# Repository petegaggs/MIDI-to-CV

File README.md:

# MIDI-to-CV
arduino based MIDI to CV converter
2 variants:
Original hardware was simple 1V/octave midi to CV converter
New version is combined Midi-CV plus AS3340 VCO module

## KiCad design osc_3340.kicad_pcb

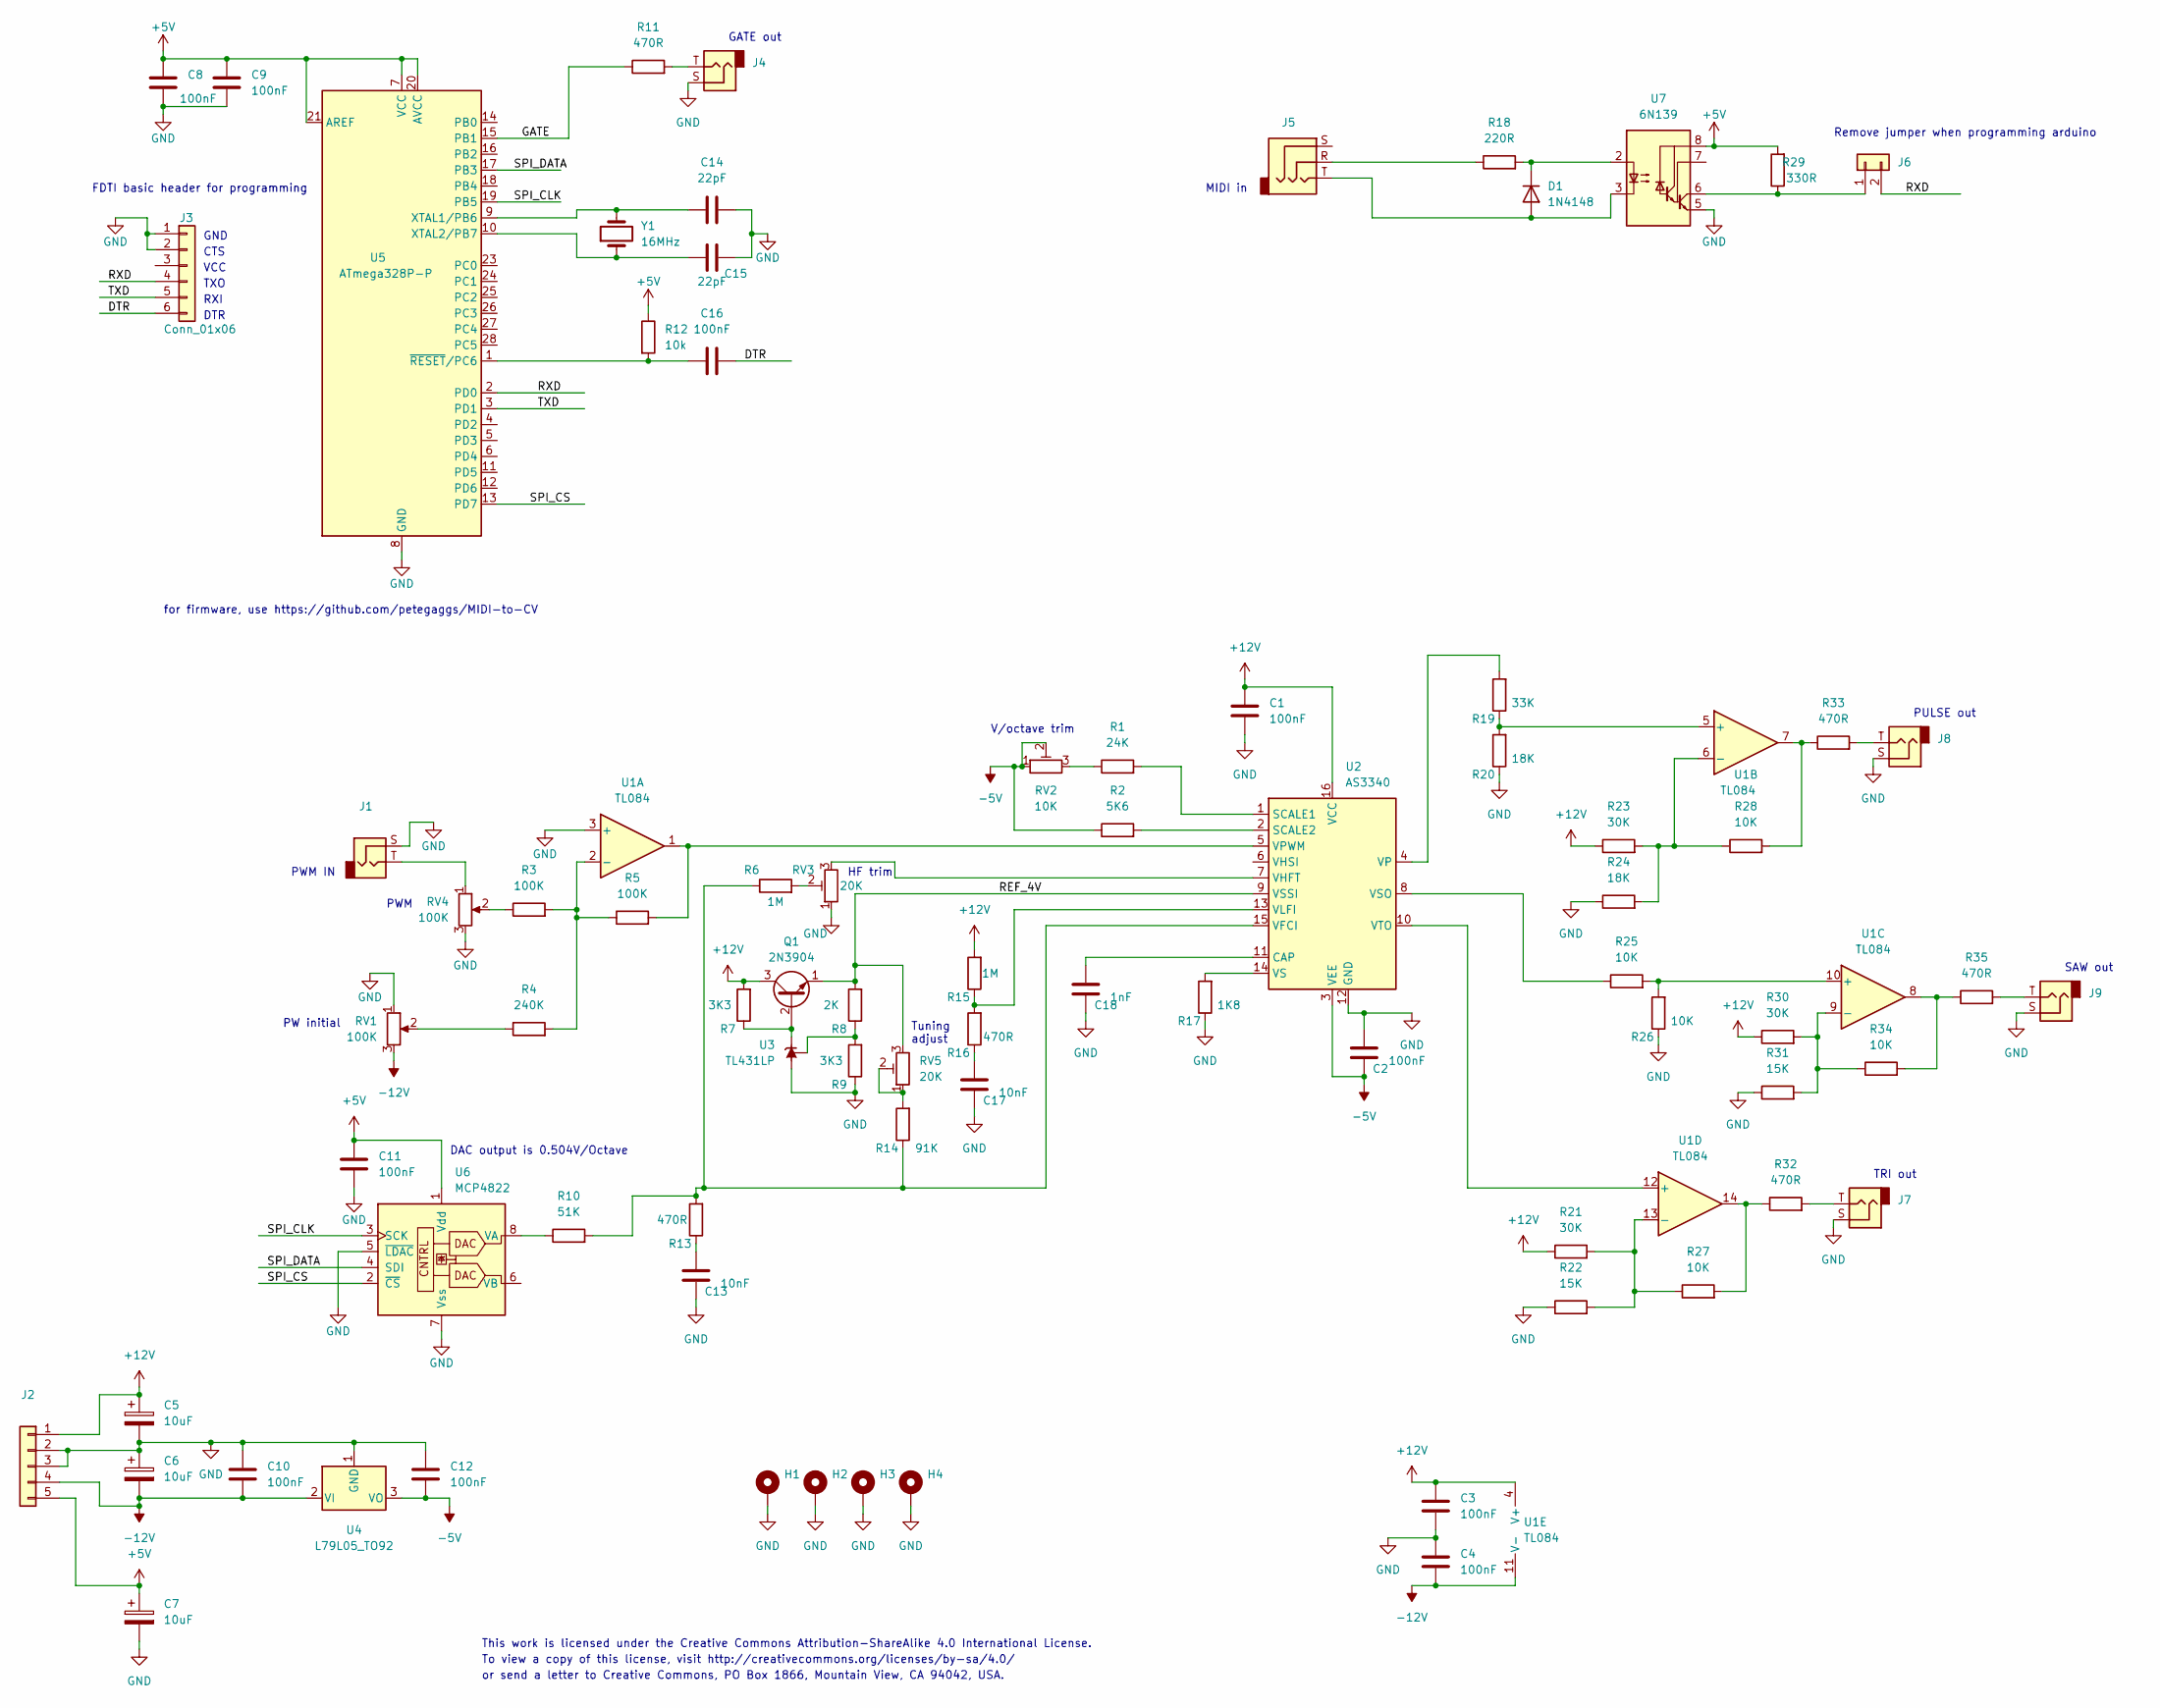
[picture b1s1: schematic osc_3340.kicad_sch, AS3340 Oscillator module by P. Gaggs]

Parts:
C1, C2, C3, C4, C8, C9, C10, C11, C12, C16: 100nF; C_0805_2012Metric_Pad1.18x1.45mm_HandSolder
C5, C6, C7: 10uF; CP_Radial_D5.0mm_P2.00mm
C13, C17: 10nF; C_0805_2012Metric_Pad1.18x1.45mm_HandSolder
C14, C15: 22pF; C_0805_2012Metric_Pad1.18x1.45mm_HandSolder
C18: 1nF; C_Disc_D6.0mm_W4.4mm_P5.00mm
D1: 1N4148; D_DO-35_SOD27_P7.62mm_Horizontal
H1, H2, H3, H4: MountingHole_Pad; MountingHole_3.2mm_M3_ISO7380_Pad
J1, J4, J7, J8, J9: AudioJack2; jack_3.5mm_mono_vertical_soundtronics_7212-239
J2: Conn_01x05; PinHeader_1x05_P2.54mm_Vertical
J3: Conn_01x06; PinHeader_1x06_P2.54mm_Vertical
J5: AudioJack3; jack_3.5mm_stereo_vertical_soundtronics_7212-240
J6: Conn_01x02; PinHeader_1x02_P2.54mm_Vertical
Q1: 2N3904; TO-92_Inline_Wide
R1: 24K; R_0805_2012Metric_Pad1.20x1.40mm_HandSolder
R2: 5K6; R_0805_2012Metric_Pad1.20x1.40mm_HandSolder
R3, R5: 100K; R_0805_2012Metric_Pad1.20x1.40mm_HandSolder
R4: 240K; R_0805_2012Metric_Pad1.20x1.40mm_HandSolder
R6, R15: 1M; R_0805_2012Metric_Pad1.20x1.40mm_HandSolder
R7, R9: 3K3; R_0805_2012Metric_Pad1.20x1.40mm_HandSolder
R8: 2K; R_0805_2012Metric_Pad1.20x1.40mm_HandSolder
R10: 51K; R_0805_2012Metric_Pad1.20x1.40mm_HandSolder
R11, R13, R16, R32, R33, R35: 470R; R_0805_2012Metric_Pad1.20x1.40mm_HandSolder
R12: 10k; R_0805_2012Metric_Pad1.20x1.40mm_HandSolder
R14: 91K; R_0805_2012Metric_Pad1.20x1.40mm_HandSolder
R17: 1K8; R_0805_2012Metric_Pad1.20x1.40mm_HandSolder
R18: 220R; R_0805_2012Metric_Pad1.20x1.40mm_HandSolder
R19: 33K; R_0805_2012Metric_Pad1.20x1.40mm_HandSolder
R20, R24: 18K; R_0805_2012Metric_Pad1.20x1.40mm_HandSolder
R21, R23, R30: 30K; R_0805_2012Metric_Pad1.20x1.40mm_HandSolder
R22, R31: 15K; R_0805_2012Metric_Pad1.20x1.40mm_HandSolder
R25, R26, R27, R28, R34: 10K; R_0805_2012Metric_Pad1.20x1.40mm_HandSolder
R29: 330R; R_0805_2012Metric_Pad1.20x1.40mm_HandSolder
RV1, RV4: 100K; Potentiometer_Alps_RK09K_Single_Vertical
RV2: 10K; Potentiometer_Bourns_3296W_Vertical
RV3, RV5: 20K; Potentiometer_Bourns_3296W_Vertical
U1: TL084; DIP-14_W7.62mm_Socket
U2: AS3340; DIP-16_W7.62mm_Socket
U3: TL431LP; TO-92_Inline_Wide
U4: L79L05_TO92; TO-92_Inline_Wide
U5: ATmega328P-P; DIP-28_W7.62mm
U6: MCP4822; DIP-8_W7.62mm_Socket
U7: 6N139; DIP-8_W7.62mm_Socket
Y1: 16MHz; Crystal_HC49-4H_Vertical

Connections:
+5V: C7.1, C8.1, C9.1, C11.1, J2.5, R12.1, R29.2, U5.7 (VCC), U5.20 (AVCC), U5.21 (AREF), U6.1 (Vdd), U7.8 (VCC)
+12V: C1.1, C3.1, C5.1, J2.1, Q1.3 (C), R7.2, R15.2, R21.1, R23.1, R30.1, U1.4 (V+), U2.16 (VCC)
-5V: C2.2, C12.2, R2.1, RV2.1, RV2.2, U2.3 (VEE), U4.3 (VO)
-12V: C4.2, C6.2, C10.2, J2.4, RV1.3, U1.11 (V-), U4.2 (VI)
/DTR: C16.2, J3.6
/GATE: R11.1, U5.15 (PB1)
/REF_4V: Q1.1 (E), R8.2, RV5.3, U2.9 (VSSI)
/RXD: J3.4, J6.2, U5.2 (PD0)
/SPI_CLK: U5.19 (PB5), U6.3 (SCK)
/SPI_CS: U5.13 (PD7), U6.2 (~CS)
/SPI_DATA: U5.17 (PB3), U6.4 (SDI)
/TXD: J3.5, U5.3 (PD1)
GND: C1.2, C2.1, C3.2, C4.1, C5.2, C6.1, C7.2, C8.2, C9.2, C10.1, C11.2, C12.1, C13.2, C14.2, C15.2, C17.2, C18.2, H1.1, H2.1, H3.1, H4.1, J1.S, J2.2, J2.3, J3.1, J3.2, J4.S, J7.S, J8.S, J9.S, R9.1, R17.1, R20.1, R22.1, R24.1, R26.1, R31.1, RV1.1, RV3.1, RV4.3, U1.3 (+), U2.12 (GND), U3.2 (A), U4.1 (GND), U5.8 (GND), U5.22 (GND), U6.5 (~LDAC), U6.7 (Vss), U7.5 (GND)
unnamed: C13.1, R13.1
unnamed: C14.1, U5.9 (XTAL1/PB6), Y1.2
unnamed: C15.1, U5.10 (XTAL2/PB7), Y1.1
unnamed: C16.1, R12.2, U5.1 (~RESET/PC6)
unnamed: C17.1, R16.1
unnamed: C18.1, U2.11 (CAP)
unnamed: D1.1 (K), R18.2, U7.2 (C1)
unnamed: D1.2 (A), J5.T, U7.3 (C2)
unnamed: J1.T, RV4.1
unnamed: J4.T, R11.2
unnamed: J5.R, R18.1
unnamed: J6.1, R29.1, U7.6 (VO2)
unnamed: J7.T, R32.2
unnamed: J8.T, R33.2
unnamed: J9.T, R35.2
unnamed: Q1.2 (B), R7.1, U3.3 (K)
unnamed: R1.1, RV2.3
unnamed: R1.2, U2.1 (SCALE1)
unnamed: R2.2, U2.2 (SCALE2)
unnamed: R3.1, RV4.2
unnamed: R3.2, R4.2, R5.1, U1.2 (-)
unnamed: R4.1, RV1.2
unnamed: R5.2, U1.1, U2.5 (VPWM)
unnamed: R6.2, RV3.2
unnamed: R8.1, R9.2, U3.1 (REF)
unnamed: R10.1, U6.8 (VA)
unnamed: R6.1, R10.2, R13.2, R14.1, U2.15 (VFCI)
unnamed: R14.2, RV5.1, RV5.2
unnamed: R15.1, R16.2, U2.13 (VLFI)
unnamed: R17.2, U2.14 (VS)
unnamed: R19.1, R20.2, U1.5 (+)
unnamed: R19.2, U2.4 (VP)
unnamed: R21.2, R22.2, R27.1, U1.13 (-)
unnamed: R23.2, R24.2, R28.1, U1.6 (-)
unnamed: R25.1, U2.8 (VSO)
unnamed: R25.2, R26.2, U1.10 (+)
unnamed: R27.2, R32.1, U1.14
unnamed: R28.2, R33.1, U1.7
unnamed: R30.2, R31.2, R34.1, U1.9 (-)
unnamed: R34.2, R35.1, U1.8
unnamed: RV3.3, U2.7 (VHFT)
unnamed: U1.12 (+), U2.10 (VTO)

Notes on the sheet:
HF trim
PWM IN
FDTI basic header for programming
for firmware, use https://github.com/petegaggs/MIDI-to-CV
GATE out
GND
V/octave trim
Tuning adjust
VCC
This work is licensed under the Creative Commons Attribution-ShareAlike 4.0 International License.
RXI
DAC output is 0.504V/Octave
TRI out
PW initial
TXO
SAW out
PWM
Remove jumper when programming arduino
or send a letter to Creative Commons, PO Box 1866, Mountain View, CA 94042, USA.
To view a copy of this license, visit http://creativecommons.org/licenses/by-sa/4.0/
PULSE out
DTR
MIDI in
CTS

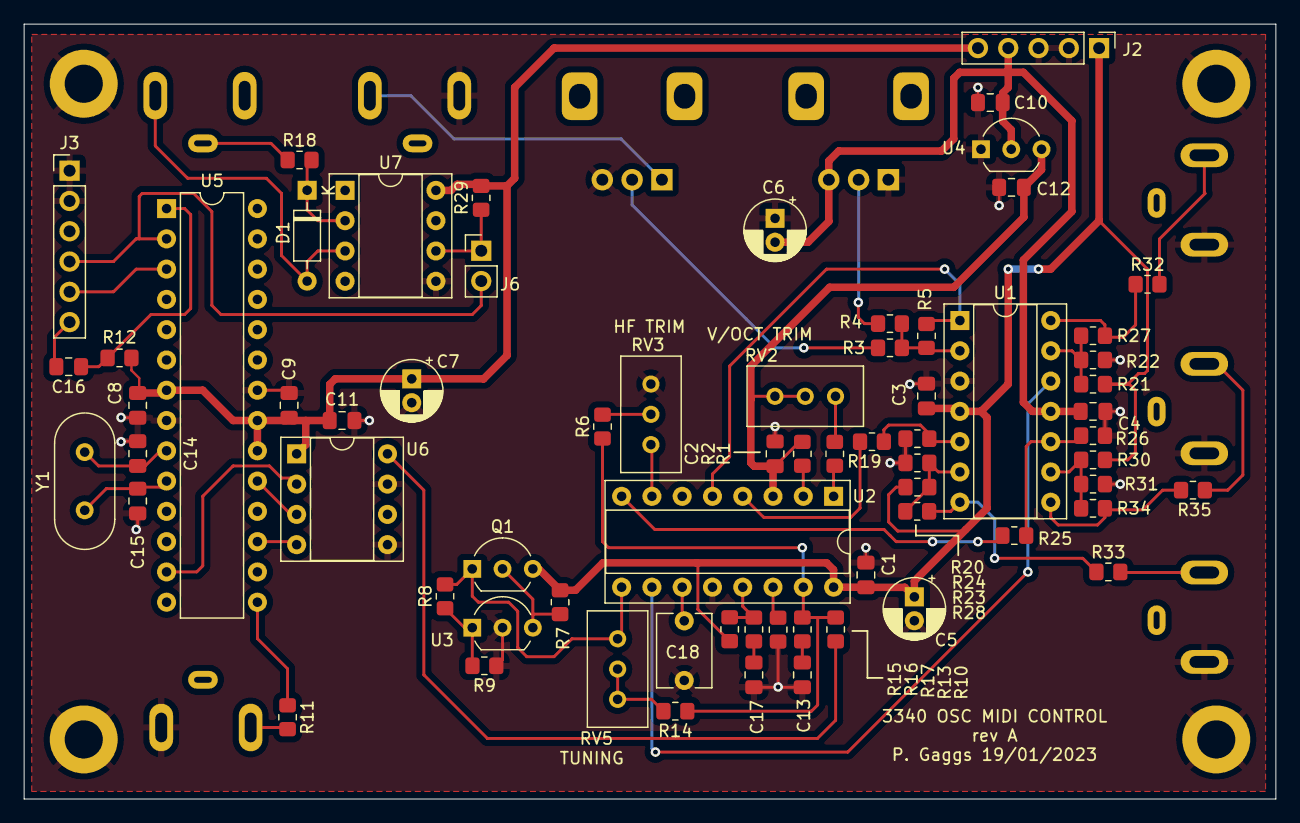
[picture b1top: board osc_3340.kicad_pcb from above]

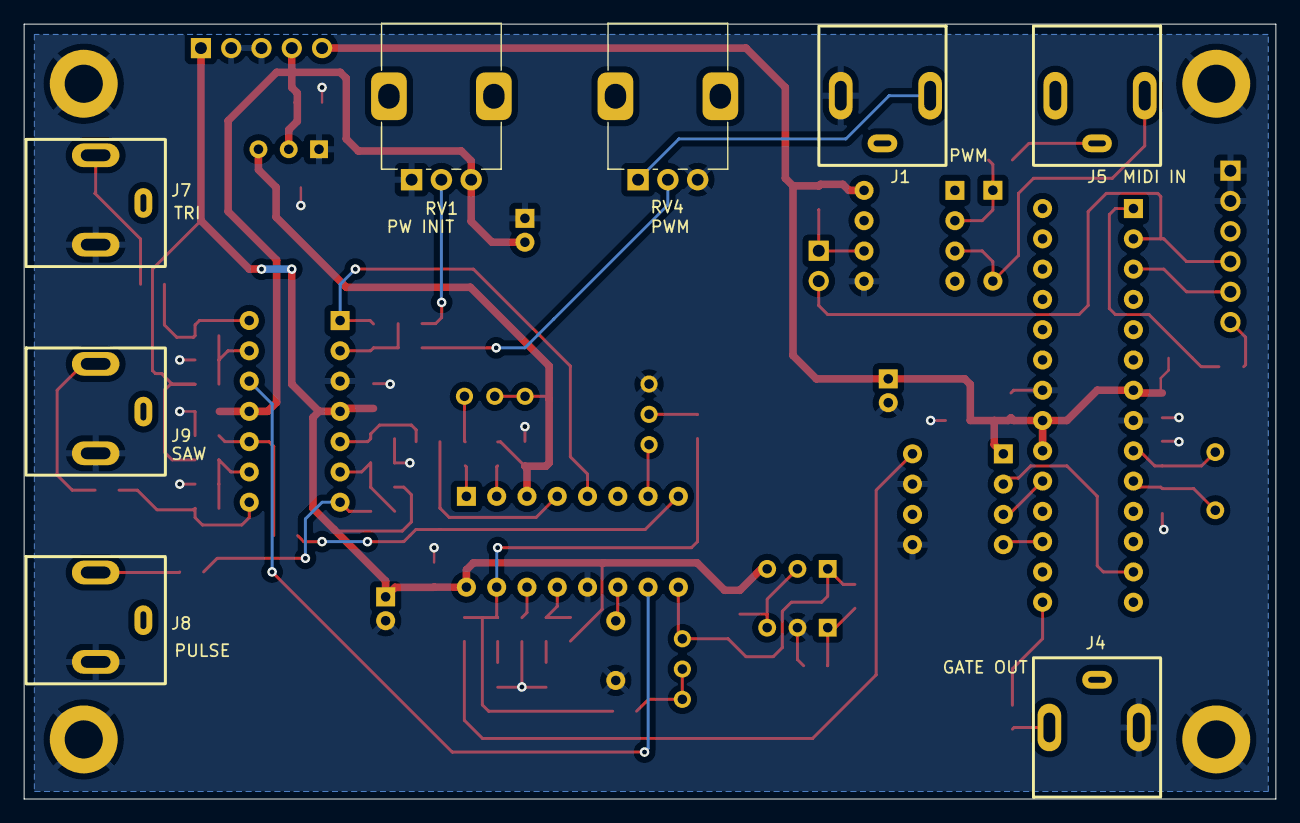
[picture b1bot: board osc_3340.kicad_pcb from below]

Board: 2 copper layers, 105.0 x 65.0 mm, 81 parts (8 on the bottom side), 55 nets.

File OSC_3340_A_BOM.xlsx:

Description | Designator | Quantity | Supplier / Part Number
OSC_3340 Bill of Materials
rev A
Capacitors
Capacitor 0805 X7R 10% 50V 100nF | C1, C2, C3, C4, C8, C9, C10, C11, C12, C16 | 10
Capacitor Electrolytic 10uF 16V 5x11mm | C5, C6, C7 | 3
Capacitor 0805 X7R 10% 50V 10nF | C13, C17 | 2
Capacitor 0805 NPO 5% 100V 22pF | C14, C15 | 2
Capacitor Polyester WIMA FKS2 1nF 5% 100V | C18 | 1
Connectors
Jack socket 3.5mm mono | J1, J4, J7, J8, J9 | 5 | Soundtronics / 7212-239
Pin header 2.54mm pitch 1x6 way | J3 | 1
Jack socket 3.5mm stereo | J5 | 1 | Soundtronics / 7212-240
Pin header 2.54mm pitch 1x2 way | J6 | 1
Semiconductors
Diode 1N4148 | D1 | 1
Transistor NPN 2N3904 TO-92 | Q1 | 1
IC Quad Op-amp TL084 DIP-14 package | U1 | 1
IC Voltage Controlled Oscillator Alfa AS3340A DIP-16 pakage | U2 | 1 | Soundtronics / 7212-601
IC Adjustable Precision shunt regulator 1% TL431ACLP TO-92 | U3 | 1 | TI / TL431ACLP
Voltage regulator -5V LM79L05 TO92 package | U4 | 1
IC Microcontroller Atmel ATMEGA328P-PU | U5 | 1
IC 12-bit dual SPI DAC MCP4822-E/P | U6 | 1 | Microchip / MCP4822-E/P
IC 6N139M Opto Isolator DIP-8 | U7 | 1
Resistors
Resistor 0805 1% 0.125W 220R | R18 | 1
Resistor 0805 1% 0.125W 330R | R29 | 1
Resistor 0805 1% 0.125W 470R | R11, R13, R16, R32, R33, R35 | 6
Resistor 0805 1% 0.125W 1K8 | R17 | 1
Resistor 0805 1% 0.125W 2K | R8 | 1
Resistor 0805 1% 0.125W 3K3 | R7, R9 | 2
Resistor 0805 1% 0.125W 5K6 | R2 | 1
Resistor 0805 1% 0.125W 10K | R12, R25, R26, R27, R28, R34 | 6
Resistor 0805 1% 0.125W 15K | R22, R31 | 2
Resistor 0805 1% 0.125W 18K | R20, R24 | 2
Resistor 0805 1% 0.125W 24K | R1 | 1
Resistor 0805 1% 0.125W 30K | R21, R23, R30 | 3
Resistor 0805 1% 0.125W 33K | R19 | 1
Resistor 0805 1% 0.125W 51K | R10 | 1
Resistor 0805 1% 0.125W 91K | R14 | 1
Resistor 0805 1% 0.125W 100K | R3, R5 | 2
Resistor 0805 1% 0.125W 240K | R4 | 1
Resistor 0805 1% 0.125W 1M | R6, R15 | 2
Poteniometer 9mm 100K linear | RV1, RV4 | 2 | Soundtronics / 7300-785
Preset Potentiometer SIL vertical Bourns 3296W 10K | RV2 | 1 | Soundtronics / 7212-857
Preset Potentiometer SIL vertical Bourns 3296W 20K | RV3, RV5 | 2 | Soundtronics / 7212-858
Crystals
Crystal HC-49 16.000MHz low profile | Y1 | 1

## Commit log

2018-01-05 Add files via upload
    work in progress.
    there are issues when playing glissando style e.g. note on received before note off, doesn't handle it
2023-04-07 updates for OSC_3340 build
